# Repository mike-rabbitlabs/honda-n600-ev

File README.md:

# Honda N600 EV Conversion

All control systems and dash UI code.

## Master Control Unit
Communicates (via CAN) to the BMS, controls fan, and coolant pumps, monitors temperature.

## Dash Screen UI

### Requirements

* [Kikad](https://www.kicad.org/)
* [Node.js/NPM](https://nodejs.org/en/download/)

### Progress
* [Leaf EM61 Motor running with Prius Gen3 inverter](https://youtu.be/WkFnErgvj8M)
* [Raspberry Pi dash screen](https://youtu.be/67Cg47E4874)
* CAN communication with chevy volt bms
* CAN communication with chevy volt charger

### Dev Setup

* Within the dash-screen/server directory, Run: _npm install_ to download dependencies
* Within the dash-screen/ui directory, Run: _npm install_ to download dependencies
* Run: _npm start_ within the dash-screen/ui directory
* Run: _npm start_ within the dash-screen/server directory
* After the build process finishes, you should see a chrome popup to http://localhost:3001
* Frontend will auto reload on ui code changes

### Production Setup
* Build the app from within the dash-screen/server directory with: _npm run build_ (builds both the frontend and hosts from the compiled react app from the app server)
* The server should now host the react app at localhost:5000 (when running the server with _npm start_)
* Configure the docker-compose.yml file with your chose parameters, and run _docker-compose up_ to start the production server

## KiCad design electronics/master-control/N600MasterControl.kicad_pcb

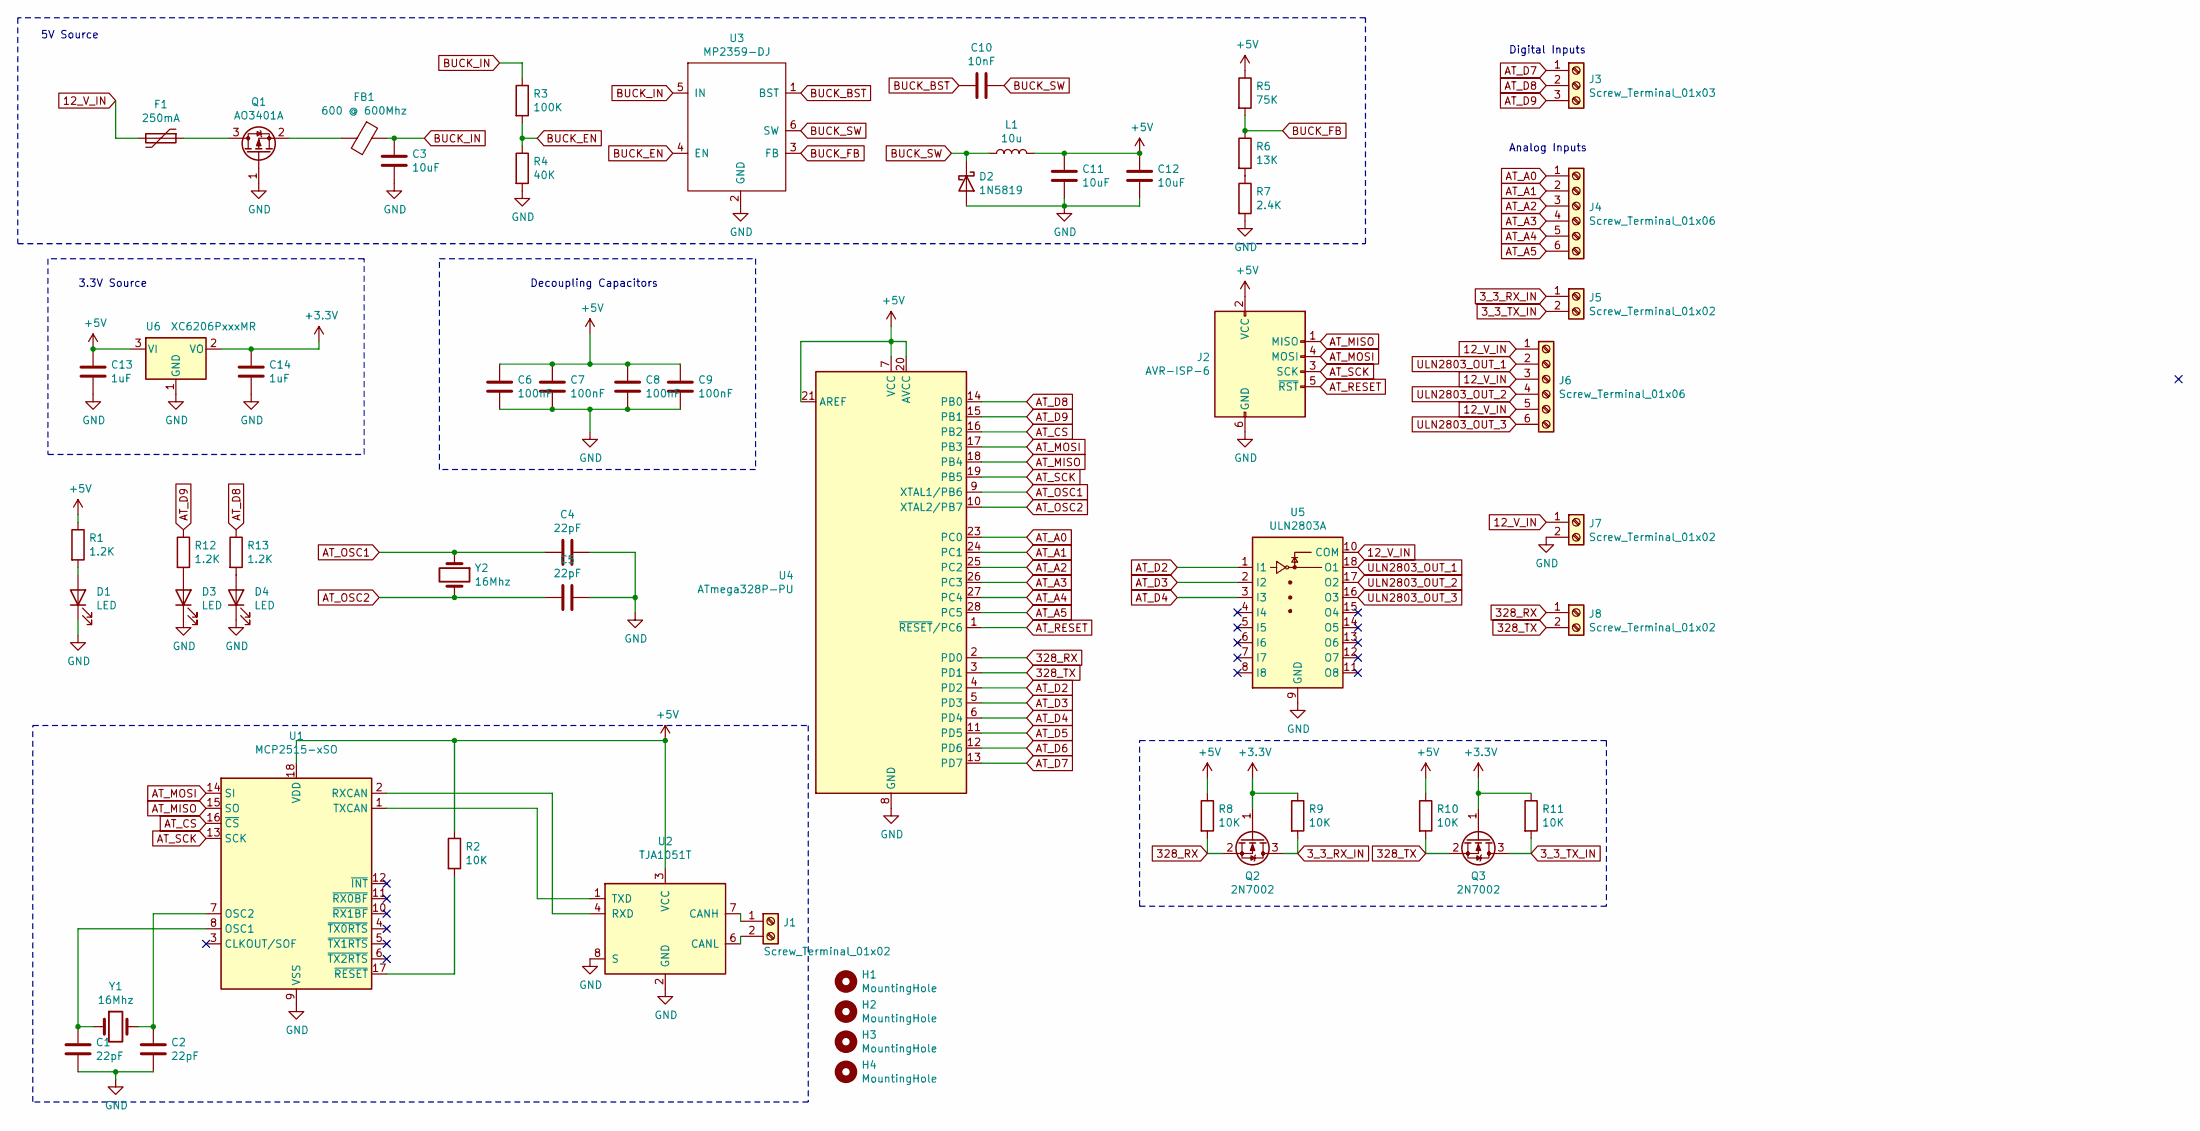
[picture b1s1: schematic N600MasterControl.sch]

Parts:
C1, C2, C4, C5: 22pF; C_0805_2012Metric; JLCPCB Part # C1804
C3, C11, C12: 10uF; C_0805_2012Metric; JLCPCB Part # C15850
C6, C7, C8, C9: 100nF; C_0805_2012Metric; JLCPCB Part # C49678
C10: 10nF; C_0805_2012Metric; JLCPCB Part # C1710
C13, C14: 1uF; C_0805_2012Metric; JLCPCB Part # C28323
D1: LED; LED_0805_2012Metric; JLCPCB Part # C84256
D2: 1N5819; D_SOD-323; JLCPCB Part # C191023
D3: LED; LED_0805_2012Metric; JLCPCB Part # C2297
D4: LED; LED_0805_2012Metric; JLCPCB Part # C2293
F1: 250mA; Fuse_1206_3216Metric; JLCPCB Part # C135334
FB1: 600 @ 600Mhz; L_0805_2012Metric; JLCPCB Part # C1017
H1, H2, H3, H4: MountingHole; MountingHole_4.3mm_M4_Pad_Via
J1, J5, J7, J8: Screw_Terminal_01x02; TerminalBlock_4Ucon_1x02_P3.50mm_Horizontal
J2: AVR-ISP-6; IDC-Header_2x03_P2.54mm_Vertical
J3: Screw_Terminal_01x03; TerminalBlock_4Ucon_1x03_P3.50mm_Horizontal
J4, J6: Screw_Terminal_01x06; TerminalBlock_4Ucon_1x06_P3.50mm_Horizontal
L1: 10u; L_0805_2012Metric; JLCPCB Part # C1046
Q1: AO3401A; SOT-23; JLCPCB Part # C15127
Q2, Q3: 2N7002; SOT-23; JLCPCB Part # C8545
R1, R12, R13: 1.2K; R_0805_2012Metric; JLCPCB Part # C17379
R2, R8, R9, R10, R11: 10K; R_0805_2012Metric; JLCPCB Part # C17414
R3: 100K; R_0603_1608Metric; JLCPCB Part # C25803
R4: 40K; R_0603_1608Metric; JLCPCB Part # C4197
R5: 75K; R_0805_2012Metric; JLCPCB Part # C17819
R6: 13K; R_0805_2012Metric; JLCPCB Part # C17455
R7: 2.4K; R_0805_2012Metric; JLCPCB Part # C17526
U1: MCP2515-xSO; SOIC-18W_7.5x11.6mm_P1.27mm
U2: TJA1051T; SOIC-8_3.9x4.9mm_P1.27mm; JLCPCB Part # C6952
U3: MP2359-DJ; SOT-23-6
U4: ATmega328P-PU; DIP-28_W7.62mm
U5: ULN2803A; SOP-18_7x12.5mm_P1.27mm; JLCPCB Part # C845537
U6: XC6206PxxxMR; SOT-23; JLCPCB Part # C5446
Y1, Y2: 16Mhz; Crystal_SMD_3225-4Pin_3.2x2.5mm; JLCPCB Part # C13738

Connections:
3_3_RX_IN: J5.1, Q2.3 (D), R9.2
3_3_TX_IN: J5.2, Q3.3 (D), R11.2
12_V_IN: F1.2, J6.1, J6.3, J6.5, J7.1, U5.10 (COM)
328_RX: J8.1, Q2.2 (S), R8.2, U4.2 (PD0)
328_TX: J8.2, Q3.2 (S), R10.2, U4.3 (PD1)
+3V3: C14.1, Q2.1 (G), Q3.1 (G), R9.1, R11.1, U6.2 (VO)
+5V: C6.1, C7.1, C8.1, C9.1, C11.1, C12.1, C13.1, J2.2 (VCC), L1.2, R1.1, R2.1, R5.1, R8.1, R10.1, U1.18 (VDD), U2.3 (VCC), U4.7 (VCC), U4.20 (AVCC), U4.21 (AREF), U6.3 (VI)
AT_A0: J4.1, U4.23 (PC0)
AT_A1: J4.2, U4.24 (PC1)
AT_A2: J4.3, U4.25 (PC2)
AT_A3: J4.4, U4.26 (PC3)
AT_A4: J4.5, U4.27 (PC4)
AT_A5: J4.6, U4.28 (PC5)
AT_CS: U1.16 (~CS), U4.16 (PB2)
AT_D2: U4.4 (PD2), U5.1 (I1)
AT_D3: U4.5 (PD3), U5.2 (I2)
AT_D4: U4.6 (PD4), U5.3 (I3)
AT_D5: U4.11 (PD5)
AT_D6: U4.12 (PD6)
AT_D7: J3.1, U4.13 (PD7)
AT_D8: J3.2, R13.1, U4.14 (PB0)
AT_D9: J3.3, R12.1, U4.15 (PB1)
AT_MISO: J2.1 (MISO), U1.15 (SO), U4.18 (PB4)
AT_MOSI: J2.4 (MOSI), U1.14 (SI), U4.17 (PB3)
AT_OSC1: C4.1, U4.9 (XTAL1/PB6), Y2.1
AT_OSC2: C5.1, U4.10 (XTAL2/PB7), Y2.2
AT_RESET: J2.5 (~RST), U4.1 (~RESET~/PC6)
AT_SCK: J2.3 (SCK), U1.13 (SCK), U4.19 (PB5)
BUCK_BST: C10.1, U3.1 (BST)
BUCK_EN: R3.2, R4.1, U3.4 (EN)
BUCK_FB: R5.2, R6.1, U3.3 (FB)
BUCK_IN: C3.1, FB1.1, R3.1, U3.5 (IN)
BUCK_SW: C10.2, D2.1 (K), L1.1, U3.6 (SW)
GND: C1.2, C2.2, C3.2, C4.2, C5.2, C6.2, C7.2, C8.2, C9.2, C11.2, C12.2, C13.2, C14.2, D1.1 (K), D2.2 (A), D3.1 (K), D4.1 (K), J2.6 (GND), J7.2, Q1.1 (G), R4.2, R7.2, U1.9 (VSS), U2.2 (GND), U2.8 (S), U3.2 (GND), U4.8 (GND), U4.22 (GND), U5.9 (GND), U6.1 (GND)
unnamed: C1.1, U1.8 (OSC1), Y1.1
unnamed: C2.1, U1.7 (OSC2), Y1.2
unnamed: D1.2 (A), R1.2
unnamed: D3.2 (A), R12.2
unnamed: D4.2 (A), R13.2
unnamed: F1.1, Q1.3 (D)
unnamed: FB1.2, Q1.2 (S)
unnamed: J1.1, U2.7 (CANH)
unnamed: J1.2, U2.6 (CANL)
unnamed: R2.2, U1.17 (~RESET)
unnamed: R6.2, R7.1
unnamed: U1.1 (TXCAN), U2.1 (TXD)
unnamed: U1.2 (RXCAN), U2.4 (RXD)
ULN2803_OUT_1: J6.2, U5.18 (O1)
ULN2803_OUT_2: J6.4, U5.17 (O2)
ULN2803_OUT_3: J6.6, U5.16 (O3)

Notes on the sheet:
Decoupling Capacitors
Analog Inputs
Digital Inputs
3.3V Source
5V Source

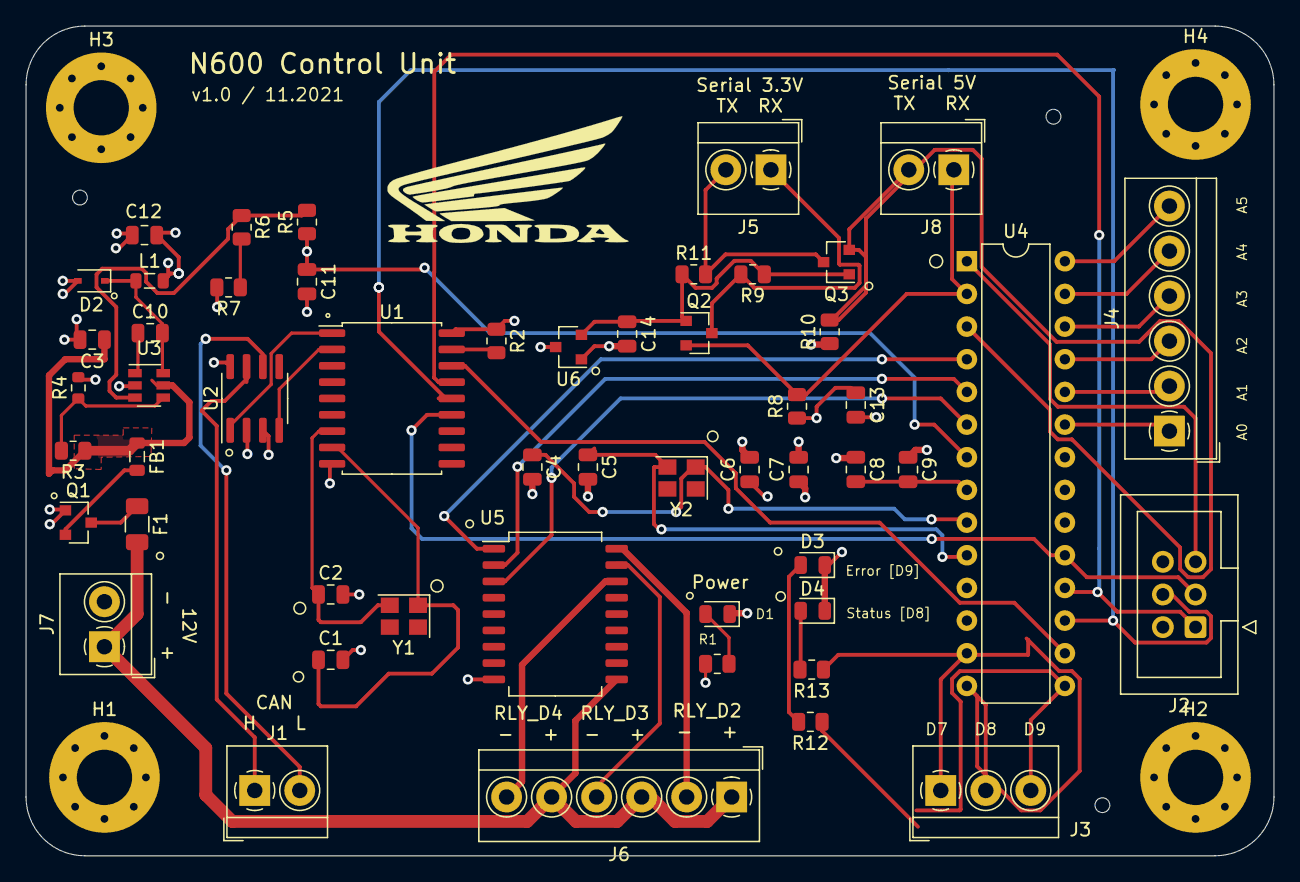
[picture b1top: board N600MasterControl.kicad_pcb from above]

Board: 4 copper layers, 97.0 x 64.5 mm, 57 parts (0 on the bottom side), 48 nets.

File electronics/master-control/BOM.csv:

Designator, Quantity, Comment, Footprint, Datasheet, JLCPCB Part #
C10 ,1,"10nF","Capacitor_SMD:C_0805_2012Metric","~","C1710"
C13 C14 ,2,"1uF","Capacitor_SMD:C_0805_2012Metric","~","C28323"
C3 C11 C12 ,3,"10uF","Capacitor_SMD:C_0805_2012Metric","~","C15850"
C1 C2 C4 C5 ,4,"22pF","Capacitor_SMD:C_0805_2012Metric","~","C1804"
C6 C7 C8 C9 ,4,"100nF","Capacitor_SMD:C_0805_2012Metric","~","C49678"
D1 D3 D4 ,3,"LED","LED_SMD:LED_0805_2012Metric","~","C84256"
D2 ,1,"1N5819","Diode_SMD:D_SOD-323","http://www.vishay.com/docs/88525/1n5817.pdf","C191023"
F1 ,1,"250mA","Fuse:Fuse_1206_3216Metric","~","C135334"
FB1 ,1,"600 @ 600Mhz","Inductor_SMD:L_0805_2012Metric","~","C1017"
H1 H2 H3 H4 ,4,"MountingHole","MountingHole:MountingHole_4.3mm_M4_Pad_Via","~"
J1 J5 J7 J8 ,4,"Screw_Terminal_01x02","TerminalBlock_4Ucon:TerminalBlock_4Ucon_1x02_P3.50mm_Horizontal","~"
J2 ,1,"AVR-ISP-6","Connector_IDC:IDC-Header_2x03_P2.54mm_Vertical"," ~"
J3 ,1,"Screw_Terminal_01x03","TerminalBlock_4Ucon:TerminalBlock_4Ucon_1x03_P3.50mm_Horizontal","~"
J4 J6 ,2,"Screw_Terminal_01x06","TerminalBlock_4Ucon:TerminalBlock_4Ucon_1x06_P3.50mm_Horizontal","~"
L1 ,1,"10u","Inductor_SMD:L_0805_2012Metric","~","C1046"
Q1 ,1,"AO3401A","Package_TO_SOT_SMD:SOT-23","http://www.aosmd.com/pdfs/datasheet/AO3401A.pdf","C15127"
Q2 Q3 ,2,"2N7002","Package_TO_SOT_SMD:SOT-23","https://www.onsemi.com/pub/Collateral/NDS7002A-D.PDF","C8545"
R1 R12 R13 ,3,"1.2K","Resistor_SMD:R_0805_2012Metric","~","C17379"
R2 R8 R9 R10 R11 ,5,"10K","Resistor_SMD:R_0805_2012Metric","~","C17414"
R3 ,1,"100K","Resistor_SMD:R_0603_1608Metric","~","C25803"
R4 ,1,"40K","Resistor_SMD:R_0603_1608Metric","~","C4197"
R5 ,1,"75K","Resistor_SMD:R_0805_2012Metric","~","C17819"
R6 ,1,"13K","Resistor_SMD:R_0805_2012Metric","~","C17455"
R7 ,1,"2.4K","Resistor_SMD:R_0805_2012Metric","~","C17526"
U1 ,1,"MCP2515-xSO","Package_SO:SOIC-18W_7.5x11.6mm_P1.27mm","http://ww1.microchip.com/downloads/en/DeviceDoc/21801e.pdf"
U2 ,1,"TJA1051T","Package_SO:SOIC-8_3.9x4.9mm_P1.27mm","http://www.nxp.com/documents/data_sheet/TJA1051.pdf","C6952"
U3 ,1,"MP2359-DJ","Package_TO_SOT_SMD:SOT-23-6",""
U4 ,1,"ATmega328P-PU","Package_DIP:DIP-28_W7.62mm","http://ww1.microchip.com/downloads/en/DeviceDoc/ATmega328_P%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"
U5 ,1,"ULN2803A","Package_SO:SOP-18_7x12.5mm_P1.27mm","http://www.ti.com/lit/ds/symlink/uln2803a.pdf","C845537"
U6 ,1,"XC6206PxxxMR","Package_TO_SOT_SMD:SOT-23","https://www.torexsemi.com/file/xc6206/XC6206.pdf","C5446"
Y1 Y2 ,2,"16Mhz","Crystal:Crystal_SMD_3225-4Pin_3.2x2.5mm","~","C13738"

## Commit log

2021-11-29 Updating README
2022-01-03 Adding CAN control scripts for chevy volt charger and bms
    Work left:
    • Integrate bms and charging code
    • Ensure we don't charge if we're running
    • Add BMS balancing commands to volt code
2022-07-31 Adding newest arduino control software
